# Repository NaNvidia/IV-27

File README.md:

# NIXIE TUBE VFD IV-27 EAGLE LIBs
Production of dual IV-27 clock.
I can not bear the responsibility that using the project.
Please use at your own risk.

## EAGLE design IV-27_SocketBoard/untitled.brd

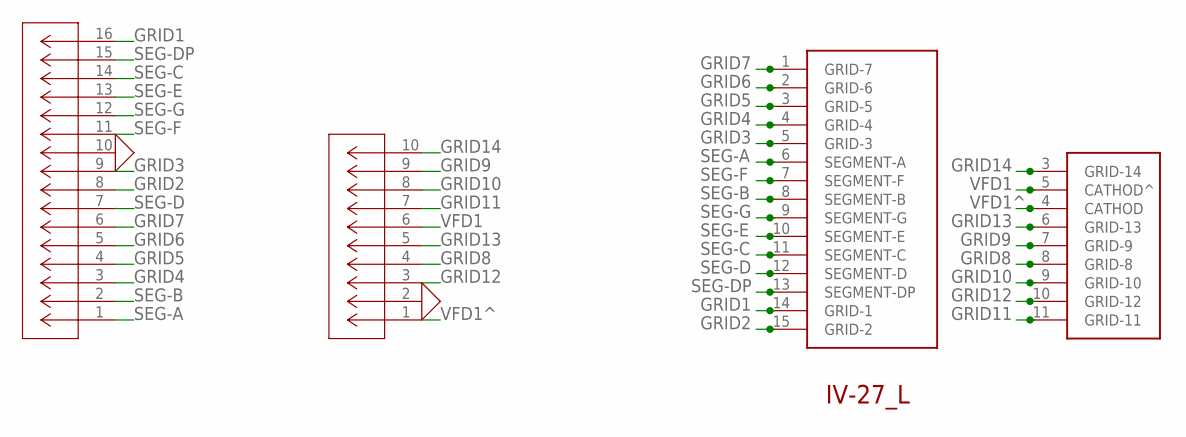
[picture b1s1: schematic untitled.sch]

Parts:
IV-27_L: 8-215079-6; CONN16_8-215079-6
IV-27_R: 8-215079-0; CONN10_8-215079-0
U$1: IV-27_L
U$2: IV-27_R

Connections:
GND: IV-27_L.10, IV-27_R.2
GRID1: IV-27_L.16, U$1.14 (GRID-1)
GRID2: IV-27_L.8, U$1.15 (GRID-2)
GRID3: IV-27_L.9, U$1.5 (GRID-3)
GRID4: IV-27_L.3, U$1.4 (GRID-4)
GRID5: IV-27_L.4, U$1.3 (GRID-5)
GRID6: IV-27_L.5, U$1.2 (GRID-6)
GRID7: IV-27_L.6, U$1.1 (GRID-7)
GRID8: IV-27_R.4, U$2.8 (GRID-8)
GRID9: IV-27_R.9, U$2.7 (GRID-9)
GRID10: IV-27_R.8, U$2.9 (GRID-10)
GRID11: IV-27_R.7, U$2.11 (GRID-11)
GRID12: IV-27_R.3, U$2.10 (GRID-12)
GRID13: IV-27_R.5, U$2.6 (GRID-13)
GRID14: IV-27_R.10, U$2.3 (GRID-14)
SEG-A: IV-27_L.1, U$1.6 (SEGMENT-A)
SEG-B: IV-27_L.2, U$1.8 (SEGMENT-B)
SEG-C: IV-27_L.14, U$1.11 (SEGMENT-C)
SEG-D: IV-27_L.7, U$1.12 (SEGMENT-D)
SEG-DP: IV-27_L.15, U$1.13 (SEGMENT-DP)
SEG-E: IV-27_L.13, U$1.10 (SEGMENT-E)
SEG-F: IV-27_L.11, U$1.7 (SEGMENT-F)
SEG-G: IV-27_L.12, U$1.9 (SEGMENT-G)
VFD1: IV-27_R.6, U$2.5 (CATHOD^)
VFD1^: IV-27_R.1, U$2.4 (CATHOD)

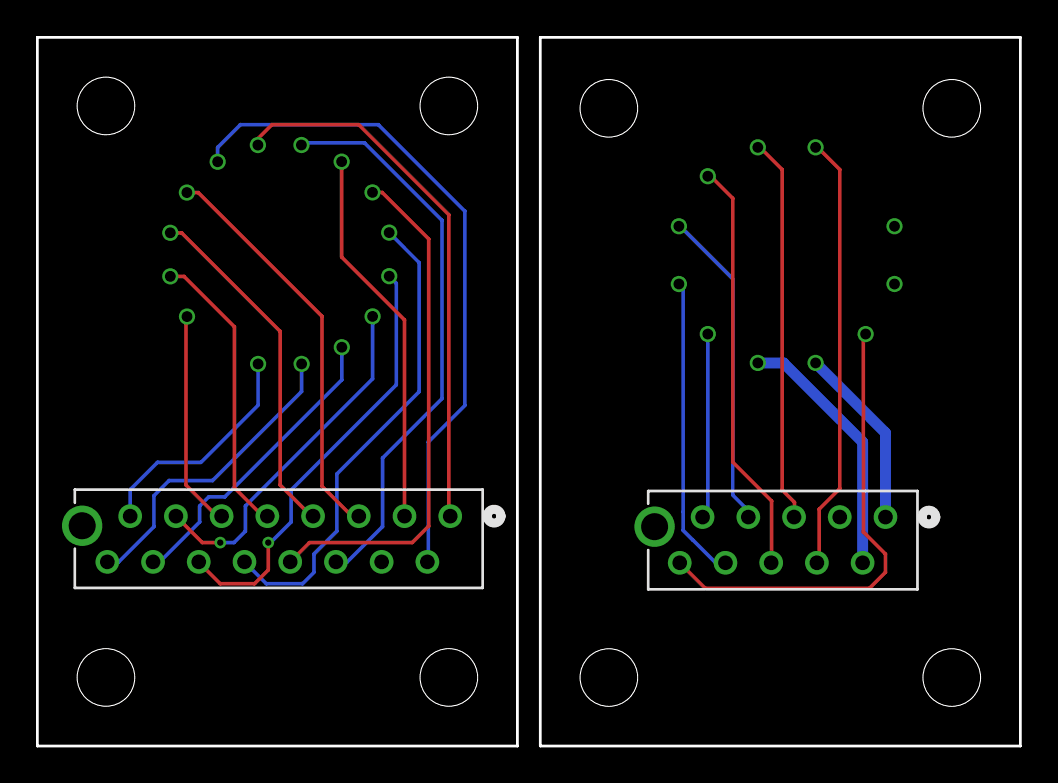
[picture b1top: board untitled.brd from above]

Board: 2 copper layers, 54.6 x 39.4 mm, 4 parts (0 on the bottom side), 25 nets.

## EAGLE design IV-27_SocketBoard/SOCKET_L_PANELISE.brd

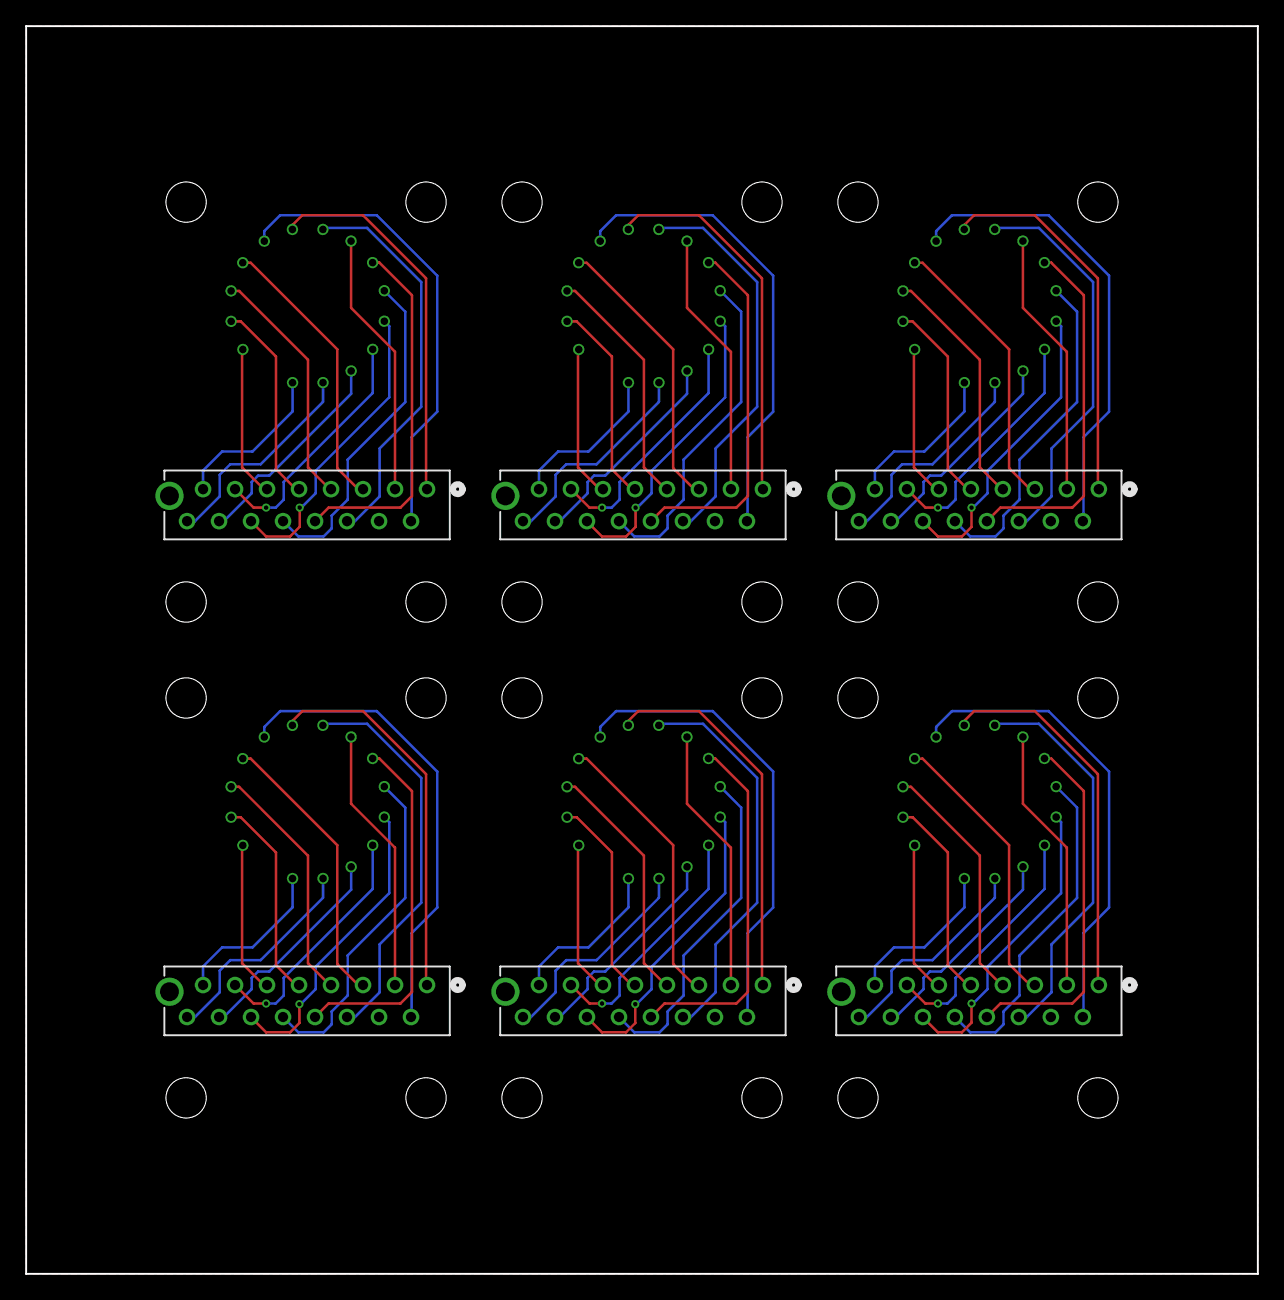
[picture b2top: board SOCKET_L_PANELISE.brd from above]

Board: 2 copper layers, 97.8 x 99.1 mm, 12 parts (0 on the bottom side), 90 nets.

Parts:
IV-27_L, IV-27_L1, IV-27_L2, IV-27_L3, IV-27_L4, IV-27_L5: 8-215079-6; CONN16_8-215079-6
U$1, U$2, U$3, U$4, U$5, U$6: IV-27_L

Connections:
GRID1: IV-27_L.16, U$1.14
GRID2: IV-27_L.8, U$1.15
GRID3: IV-27_L.9, U$1.5
GRID4: IV-27_L.3, U$1.4
GRID5: IV-27_L.4, U$1.3
GRID6: IV-27_L.5, U$1.2
GRID7: IV-27_L.6, U$1.1
GRID8: IV-27_L1.16, U$2.14
GRID9: IV-27_L1.8, U$2.15
GRID10: IV-27_L1.9, U$2.5
GRID11: IV-27_L1.3, U$2.4
GRID12: IV-27_L1.4, U$2.3
GRID13: IV-27_L1.5, U$2.2
GRID14: IV-27_L1.6, U$2.1
GRID15: IV-27_L2.16, U$3.14
GRID16: IV-27_L2.8, U$3.15
GRID17: IV-27_L2.9, U$3.5
GRID18: IV-27_L2.3, U$3.4
GRID19: IV-27_L2.4, U$3.3
GRID20: IV-27_L2.5, U$3.2
GRID21: IV-27_L2.6, U$3.1
GRID22: IV-27_L3.16, U$4.14
GRID23: IV-27_L3.8, U$4.15
GRID24: IV-27_L3.9, U$4.5
GRID25: IV-27_L3.3, U$4.4
GRID26: IV-27_L3.4, U$4.3
GRID27: IV-27_L3.5, U$4.2
GRID28: IV-27_L3.6, U$4.1
GRID29: IV-27_L4.16, U$5.14
GRID30: IV-27_L4.8, U$5.15
GRID31: IV-27_L4.9, U$5.5
GRID32: IV-27_L4.3, U$5.4
GRID33: IV-27_L4.4, U$5.3
GRID34: IV-27_L4.5, U$5.2
GRID35: IV-27_L4.6, U$5.1
GRID36: IV-27_L5.16, U$6.14
GRID37: IV-27_L5.8, U$6.15
GRID38: IV-27_L5.9, U$6.5
GRID39: IV-27_L5.3, U$6.4
GRID40: IV-27_L5.4, U$6.3
GRID41: IV-27_L5.5, U$6.2
GRID42: IV-27_L5.6, U$6.1
SEG-A: IV-27_L.1, U$1.6
SEG-A1: IV-27_L1.1, U$2.6
SEG-A2: IV-27_L2.1, U$3.6
SEG-A3: IV-27_L3.1, U$4.6
SEG-A4: IV-27_L4.1, U$5.6
SEG-A5: IV-27_L5.1, U$6.6
SEG-B: IV-27_L.2, U$1.8
SEG-B1: IV-27_L1.2, U$2.8
SEG-B2: IV-27_L2.2, U$3.8
SEG-B3: IV-27_L3.2, U$4.8
SEG-B4: IV-27_L4.2, U$5.8
SEG-B5: IV-27_L5.2, U$6.8
SEG-C: IV-27_L.14, U$1.11
SEG-C1: IV-27_L1.14, U$2.11
SEG-C2: IV-27_L2.14, U$3.11
SEG-C3: IV-27_L3.14, U$4.11
SEG-C4: IV-27_L4.14, U$5.11
SEG-C5: IV-27_L5.14, U$6.11
SEG-D: IV-27_L.7, U$1.12
SEG-D1: IV-27_L1.7, U$2.12
SEG-D2: IV-27_L2.7, U$3.12
SEG-D3: IV-27_L3.7, U$4.12
SEG-D4: IV-27_L4.7, U$5.12
SEG-D5: IV-27_L5.7, U$6.12
SEG-DP: IV-27_L.15, U$1.13
SEG-DP1: IV-27_L1.15, U$2.13
SEG-DP2: IV-27_L2.15, U$3.13
SEG-DP3: IV-27_L3.15, U$4.13
SEG-DP4: IV-27_L4.15, U$5.13
SEG-DP5: IV-27_L5.15, U$6.13
SEG-E: IV-27_L.13, U$1.10
SEG-E1: IV-27_L1.13, U$2.10
SEG-E2: IV-27_L2.13, U$3.10
SEG-E3: IV-27_L3.13, U$4.10
SEG-E4: IV-27_L4.13, U$5.10
SEG-E5: IV-27_L5.13, U$6.10
SEG-F: IV-27_L.11, U$1.7
SEG-F1: IV-27_L1.11, U$2.7
SEG-F2: IV-27_L2.11, U$3.7
SEG-F3: IV-27_L3.11, U$4.7
SEG-F4: IV-27_L4.11, U$5.7
SEG-F5: IV-27_L5.11, U$6.7
SEG-G: IV-27_L.12, U$1.9
SEG-G1: IV-27_L1.12, U$2.9
SEG-G2: IV-27_L2.12, U$3.9
SEG-G3: IV-27_L3.12, U$4.9
SEG-G4: IV-27_L4.12, U$5.9
SEG-G5: IV-27_L5.12, U$6.9

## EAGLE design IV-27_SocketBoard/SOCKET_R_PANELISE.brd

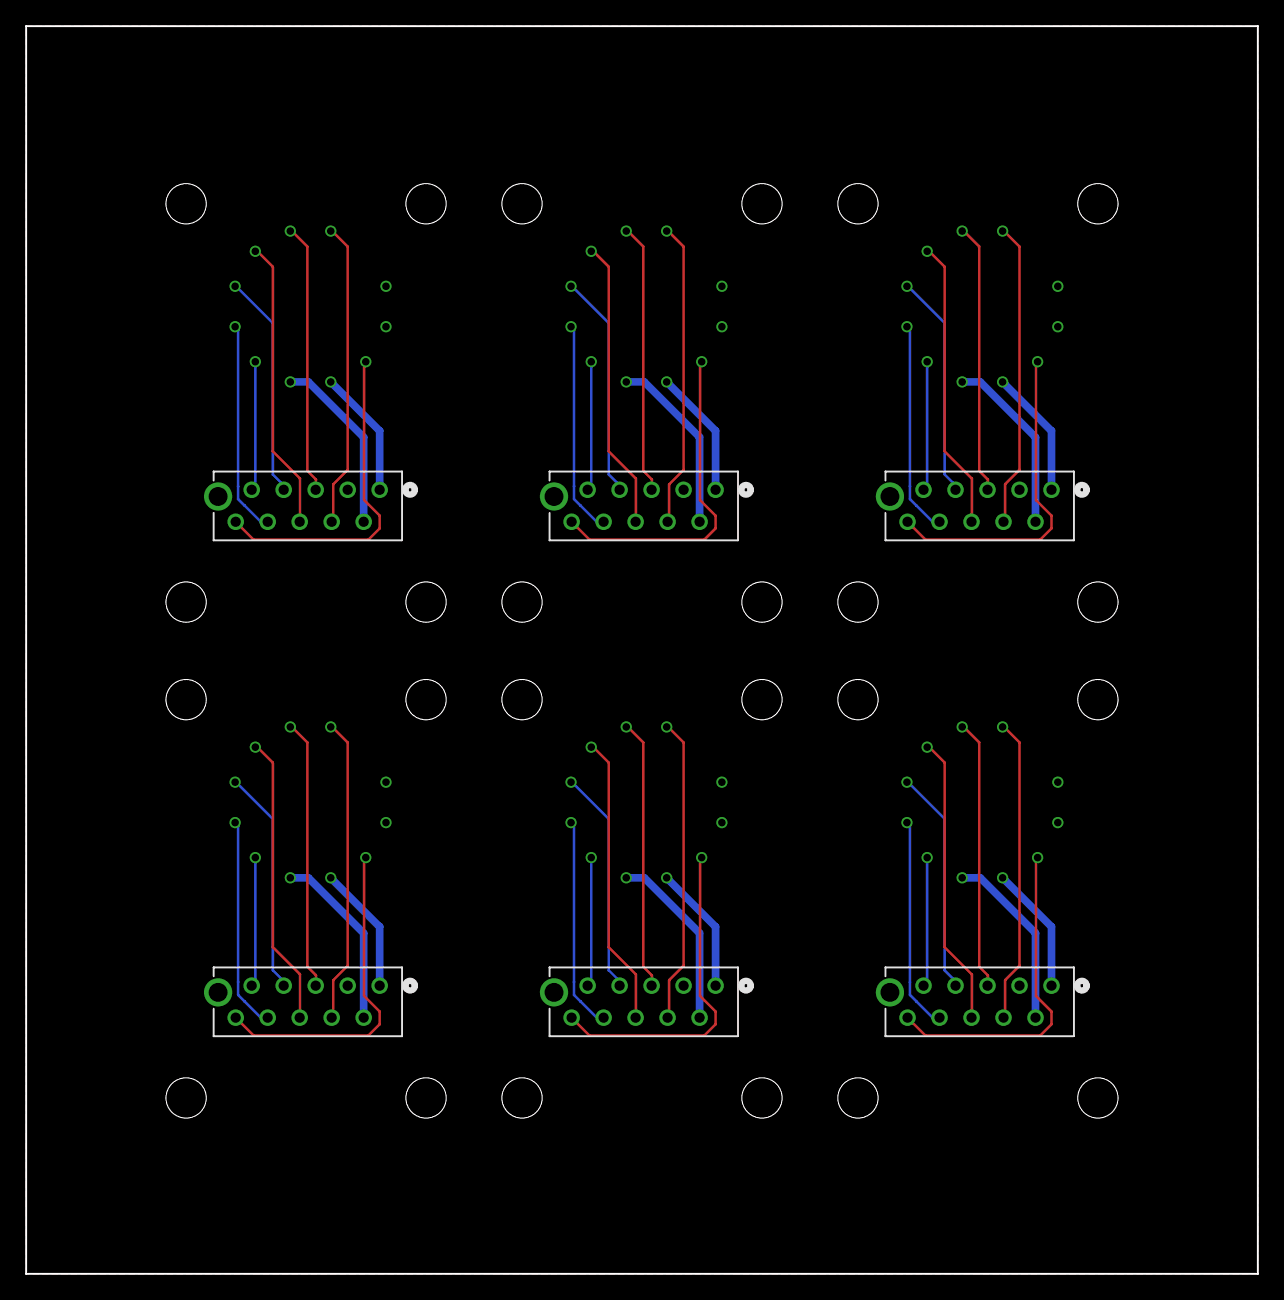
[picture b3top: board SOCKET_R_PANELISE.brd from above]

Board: 2 copper layers, 97.8 x 99.1 mm, 12 parts (0 on the bottom side), 54 nets.

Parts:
IV-27_R, IV-27_R1, IV-27_R2, IV-27_R3, IV-27_R4, IV-27_R5: 8-215079-0; CONN10_8-215079-0
U$1, U$2, U$3, U$4, U$5, U$6: IV-27_R

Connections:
GRID1: IV-27_R1.3, U$1.10
GRID2: IV-27_R1.4, U$1.8
GRID3: IV-27_R1.5, U$1.6
GRID4: IV-27_R1.7, U$1.11
GRID5: IV-27_R1.8, U$1.9
GRID6: IV-27_R1.9, U$1.7
GRID7: IV-27_R1.10, U$1.3
GRID8: IV-27_R.4, U$2.8
GRID9: IV-27_R.9, U$2.7
GRID10: IV-27_R.8, U$2.9
GRID11: IV-27_R.7, U$2.11
GRID12: IV-27_R.3, U$2.10
GRID13: IV-27_R.5, U$2.6
GRID14: IV-27_R.10, U$2.3
GRID15: IV-27_R2.3, U$3.10
GRID16: IV-27_R2.4, U$3.8
GRID17: IV-27_R2.5, U$3.6
GRID18: IV-27_R2.7, U$3.11
GRID19: IV-27_R2.8, U$3.9
GRID20: IV-27_R2.9, U$3.7
GRID21: IV-27_R2.10, U$3.3
GRID22: IV-27_R3.3, U$4.10
GRID23: IV-27_R3.4, U$4.8
GRID24: IV-27_R3.5, U$4.6
GRID25: IV-27_R3.7, U$4.11
GRID26: IV-27_R3.8, U$4.9
GRID27: IV-27_R3.9, U$4.7
GRID28: IV-27_R3.10, U$4.3
GRID29: IV-27_R4.3, U$5.10
GRID30: IV-27_R4.4, U$5.8
GRID31: IV-27_R4.5, U$5.6
GRID32: IV-27_R4.7, U$5.11
GRID33: IV-27_R4.8, U$5.9
GRID34: IV-27_R4.9, U$5.7
GRID35: IV-27_R4.10, U$5.3
GRID36: IV-27_R5.3, U$6.10
GRID37: IV-27_R5.4, U$6.8
GRID38: IV-27_R5.5, U$6.6
GRID39: IV-27_R5.7, U$6.11
GRID40: IV-27_R5.8, U$6.9
GRID41: IV-27_R5.9, U$6.7
GRID42: IV-27_R5.10, U$6.3
VFD1: IV-27_R.6, U$2.5
VFD1^: IV-27_R.1, U$2.4
VFD1^1: IV-27_R1.1, U$1.4
VFD1^2: IV-27_R2.1, U$3.4
VFD1^3: IV-27_R3.1, U$4.4
VFD1^4: IV-27_R4.1, U$5.4
VFD1^5: IV-27_R5.1, U$6.4
VFD2: IV-27_R1.6, U$1.5
VFD3: IV-27_R2.6, U$3.5
VFD4: IV-27_R3.6, U$4.5
VFD5: IV-27_R4.6, U$5.5
VFD6: IV-27_R5.6, U$6.5

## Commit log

2019-04-16 Add files via upload
    IV-27 EAGLE LIB
2019-04-16 IV-27 SOCKET BOARD
2019-04-30 Update LICENSE
2020-03-17 IV-27L
2020-03-17 IV-27R
2020-03-17 case:Use CNC
